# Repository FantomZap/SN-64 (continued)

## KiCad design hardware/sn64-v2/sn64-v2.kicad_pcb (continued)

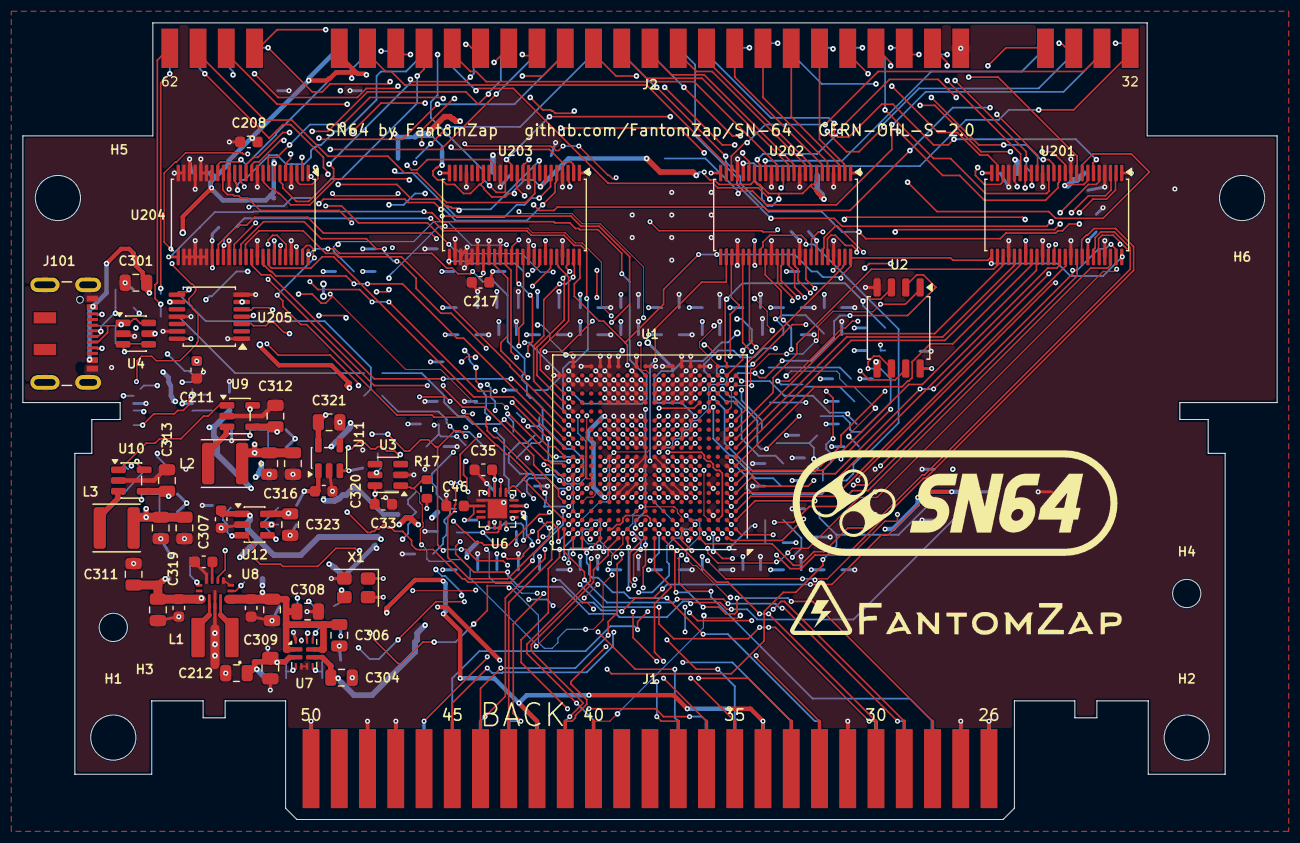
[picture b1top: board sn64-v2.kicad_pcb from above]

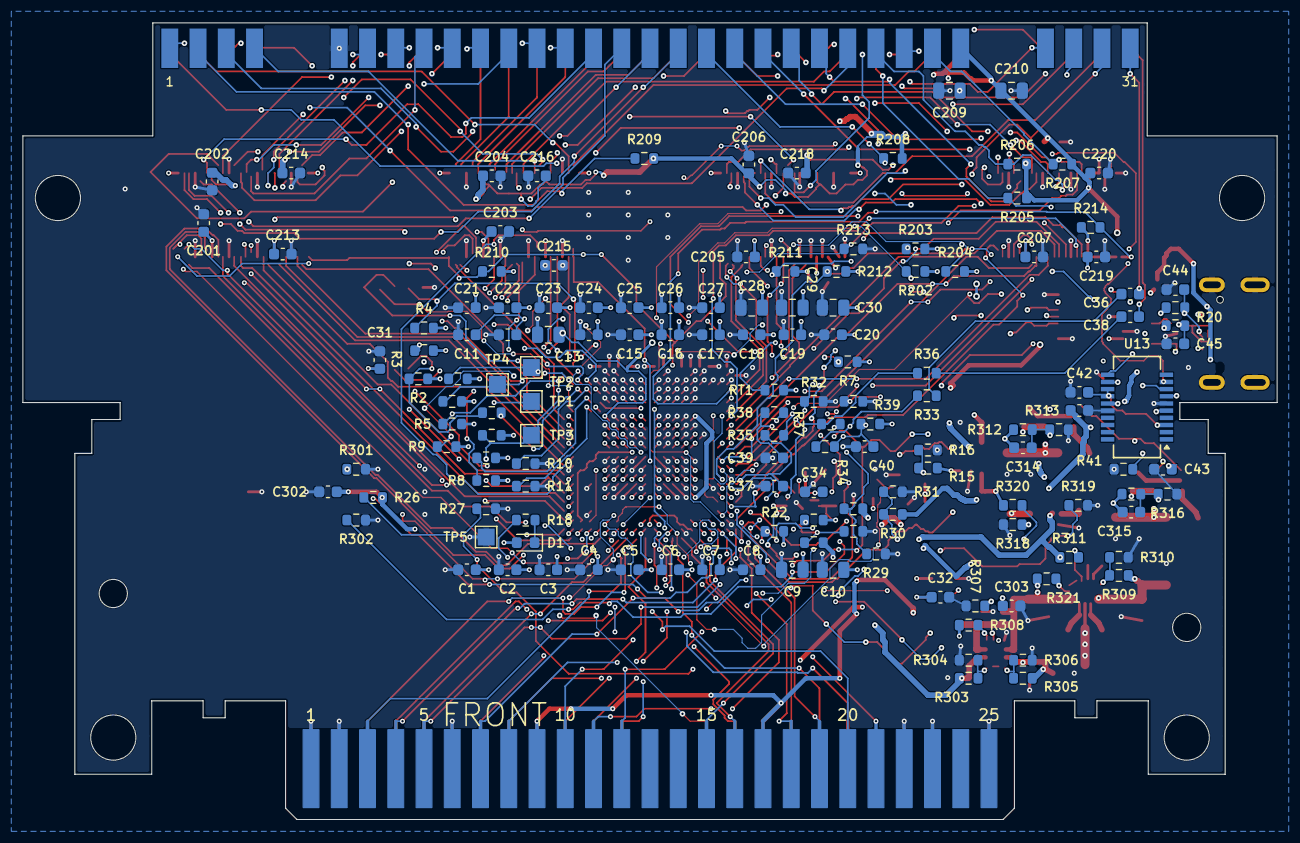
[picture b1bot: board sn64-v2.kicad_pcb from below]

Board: 6 copper layers, 111.0 x 70.5 mm, 200 parts (142 on the bottom side), 221 nets.

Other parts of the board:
H1, H2, H5, H6: MountingHole_4mm
H3, H4: MountingHole_2.5mm

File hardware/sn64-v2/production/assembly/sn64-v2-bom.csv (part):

Item,Designator,Qty,Manufacturer,Mfg Part #,Description / Value,Package / Footprint,Type,Side,LCSC or other source #,Substitute allowed,Notes
1,"C1, C2, C3, C4, C5, C6, C7, C8, C11, C12, C14, C15, C16, C17, C18, C19, C20, C21, C22, C23, C24, C25, C26, C27, C31, C32, C33, C41, C42, C43, C201, C202, C203, C204, C205, C206, C207, C208, C211, C213, C214, C215, C216, C217, C218, C219, C220, C307, C322",49,YAGEO,CC0603KRX7R9BB104,100 nF 50 V X7R 10 % 0603,0603,SMD,bottom and top,C14663,"yes: same value, size and dielectric, same voltage or higher",
2,"C9, C10, C13, C28, C29, C30, C212, C305, C306, C308, C323",11,Samsung Electro-Mechanics,CL21A106KAYNNNE,10 uF 25 V X5R 10 % 0805,0805,SMD,bottom and top,C15850,"yes: same value, size and dielectric, same voltage or higher",
3,"C34, C35, C36, C38, C40, C46, C302, C320",8,Samsung Electro-Mechanics,CL10A105KB8NNNC,1 uF 50 V X5R 10 % 0603,0603,SMD,bottom and top,C15849,"yes: same value, size and dielectric, same voltage or higher",
4,"C37, C39",2,Samsung Electro-Mechanics,CL10C102JB8NNNC,1 nF 50 V C0G 5 % 0603,0603,SMD,bottom,C163508,"yes: same value, size and dielectric, same voltage or higher",
5,"C44, C45",2,Samsung Electro-Mechanics,CL10C470JB8NNNC,47 pF 50 V C0G 5 % 0603,0603,SMD,bottom,C1671,"yes: same value, size and dielectric, same voltage or higher",
6,"C209, C210, C309, C310, C311, C312, C313, C316, C317, C318, C319",11,Samsung Electro-Mechanics,CL21A226MAQNNNE,22 uF 25 V X5R 20 % 0805,0805,SMD,bottom and top,C45783,"yes: same value, size and dielectric, same voltage or higher",
7,C301,1,Samsung Electro-Mechanics,CL21A225KBQNNNE,2.2 uF 50 V X5R 10 % 0805,0805,SMD,top,C377773,"yes: same value, size and dielectric, same voltage or higher",
8,C303,1,FH (Fenghua),0603B103K500NT,10 nF 50 V X7R 10 % 0603,0603,SMD,bottom,C57112,"yes: same value, size and dielectric, same voltage or higher",
9,"C304, C321",2,Samsung Electro-Mechanics,CL21A475KAQNNNE,4.7 uF 25 V X5R 10 % 0805,0805,SMD,top,C1779,"yes: same value, size and dielectric, same voltage or higher",
10,"C314, C315",2,FH (Fenghua),0603CG6R8C500NT,6.8 pF 50 V C0G 0.25 pF 0603,0603,SMD,bottom,C1679,"yes: same value, size and dielectric, same voltage or higher",
11,"C324, C325",2,Samsung Electro-Mechanics,CL10A106MA8NRNC,10 uF 25 V X5R 20 % 0603,0603,SMD,top,C96446,"yes: same value, size and dielectric, same voltage or higher",
12,D1,1,Everlight,19-21SYGC/S530-E2/4T,"LED yellow-green 573 nm, 2.0 V, 0603",0603,SMD,bottom,C2986011,yes: any yellow-green 0603 lamp with about 2 V across it,
13,J101,1,JAE,DX07S016JA3R1500,DX07S016JA3R1500. USB 2.0-only Type-C Receptacle connector,"USB-C receptacle, 16 pads and 4 legs in plated slots",SMD,top,C2939926,no,USB-C: surface-mount pads and four legs in plated slots
14,L1,1,APV,PNR4020-1R5M,1.5uH PNR4020-1R5M. Inductor,4 x 4 x 2 mm inductor,SMD,top,C54620133,no,
15,"L2, L3",2,Changjiang Microelectronics,FNR4030S2R2MT,2.2uH FNR4030S2R2MT. Inductor,4 x 4 x 3 mm inductor,SMD,top,C167869,no,
16,R1,1,UNI-ROYAL,0603WAF330JT5E,33 ohm 1 % 0603,0603,SMD,bottom,C23140,"yes: same value, size and tolerance",
17,"R2, R18",2,UNI-ROYAL,0603WAF1001T5E,1 k 1 % 0603,0603,SMD,bottom,C21190,"yes: same value, size and tolerance",
18,"R3, R6, R7, R8, R9, R12, R13, R14, R22, R23, R41, R205, R206, R207, R208",15,UNI-ROYAL,0603WAF4701T5E,4.7 k 1 % 0603,0603,SMD,bottom,C23162,"yes: same value, size and tolerance",
19,"R4, R5, R10, R11, R17, R24, R25, R27, R29, R31, R32, R33, R34, R35, R36, R37, R38, R39, R40, R202, R203, R204, R209, R308, R320, R321",26,UNI-ROYAL,0603WAF1002T5E,10 k 1 % 0603,0603,SMD,bottom and top,C25804,"yes: same value, size and tolerance",
20,R15,1,FOJAN,FRC0603F6493TS,649 k 1 % 0603,0603,SMD,bottom,C2999594,"yes: same value, size and tolerance",
21,"R16, R210, R211, R212, R213, R214, R304, R306, R311, R319",10,UNI-ROYAL,0603WAF1003T5E,100 k 1 % 0603,0603,SMD,bottom,C25803,"yes: same value, size and tolerance",
22,"R19, R20",2,UNI-ROYAL,0603WAF270JT5E,27 ohm 1 % 0603,0603,SMD,bottom,C25190,"yes: same value, size and tolerance",
23,"R26, R28, R30",3,UNI-ROYAL,0603WAF2002T5E,20 k 1 % 0603,0603,SMD,bottom,C4184,"yes: same value, size and tolerance",
24,"R301, R302",2,UNI-ROYAL,0603WAF5101T5E,5.1 k 1 % 0603,0603,SMD,bottom,C23186,"yes: same value, size and tolerance",
25,R303,1,FOJAN,FRC0603F2743TS,274 k 1 % 0603,0603,SMD,bottom,C5126128,"yes: same value, size and tolerance",
26,R305,1,FOJAN,FRC0603F1823TS,182 k 1 % 0603,0603,SMD,bottom,C5126102,"yes: same value, size and tolerance",
27,R307,1,FOJAN,FRC0603F4422TS,44.2 k 1 % 0603,0603,SMD,bottom,C2930103,"yes: same value, size and tolerance",
28,R309,1,YAGEO,RT0603BRD07232KL,232 k 0.1 % 25 ppm thin film 0603,0603,SMD,bottom,C861240,"yes: same value, size and tolerance",
29,R310,1,YAGEO,RT0603BRD0744K2L,44.2 k 0.1 % 25 ppm thin film 0603,0603,SMD,bottom,C861410,"yes: same value, size and tolerance",
30,R312,1,YAGEO,RT0603BRD07459KL,459 k 0.1 % 25 ppm thin film 0603,0603,SMD,bottom,C6288321,"yes: same value, size and tolerance",
31,R313,1,YAGEO,RT0603BRD07102KL,102 k 0.1 % 25 ppm thin film 0603,0603,SMD,bottom,C861068,"yes: same value, size and tolerance",
32,R315,1,YAGEO,RT0603BRD07100KL,100 k 0.1 % 25 ppm thin film 0603,0603,SMD,bottom,C122538,"yes: same value, size and tolerance",
33,R316,1,YAGEO,RT0603BRD07120KL,120 k 0.1 % 25 ppm thin film 0603,0603,SMD,bottom,C705720,"yes: same value, size and tolerance",
34,R318,1,UNI-ROYAL,0603WAF2492T5E,24.9 k 1 % 0603,0603,SMD,bottom,C25962,"yes: same value, size and tolerance",
35,RT1,1,Sunlord,SDNT1608X103F3950FTF,"NTC 10 k 1 %, B(25/50) 3950 K 1 %, 0603",0603,SMD,bottom,C279936,"yes: 10 k, 1 %, B(25/50) 3950 K, 0603",
36,U1,1,Lattice Semiconductor,LFE5U-85F-8BG381I,"LFE5U-85F-8BG381I. ECP5 FPGA, 84K LUTs, 1.2V, BGA-381","caBGA-381, 0.8 mm pitch",SMD,top,Mouser 842-LFE5U85F8BG381I,no,
37,U2,1,Winbond,W25Q128JVSIQ,"W25Q128JVSIQ. 128Mbit / 16MiB Serial Flash Memory, Standard/Dual/Quad SPI, 2.7-3.6V, SOIC-8","SOIC-8, 5.3 mm body",SMD,top,C97521,no,
38,U3,1,Texas Instruments,TPS3808G01DBVR,"TPS3808G01DBVR. Low-Quiescent-Current, Programmable-Delay Supervisory Circuit, SOT-23-6",SOT-23-6,SMD,top,C19653,no,
39,U4,1,STMicroelectronics,USBLC6-2SC6,"USBLC6-2SC6. Very low capacitance ESD protection diode, 2 data-line, SOT-23-6",SOT-23-6,SMD,top,C7519,no,
40,U6,1,Texas Instruments,TLA2528IRTER,"TLA2528IRTER. 8-channel 12-bit I2C ADC, WQFN-16","WQFN-16, 3 x 3 mm, 0.5 mm pitch",SMD,top,C2866175,no,
41,U7,1,Texas Instruments,TPS2121RUXR,"TPS2121RUXR. 2.8-22 V priority power mux, 4.5 A, current limit, VQFN-HR-12","VQFN-HR-12, 2 x 2.5 mm",SMD,top,C485916,no,
42,U8,1,Texas Instruments,TPS63070RNMR,"TPS63070RNMR. 2-16 V input buck-boost converter, adjustable output, power good","VQFN-HR-15, 2.5 x 3 mm",SMD,top,C109322,no,
43,"U9, U10",2,Texas Instruments,TLV62569DBVR,"TLV62569DBVR. High Efficiency Synchronous Buck Converter, Adjustable Output 0.6V-5.5V, 2A, SOT-23-5",SOT-23-5,SMD,top,C141836,no,
44,U11,1,Diodes Incorporated,AP2112K-2.5TRG1,"AP2112K-2.5TRG1. 600mA low dropout linear regulator, with enable pin, 3V-6V input voltage range, 2.5V fixed positive output, SOT-23-5",SOT-23-5,SMD,top,C51118,no,
45,U12,1,Texas Instruments,TPS2553DBVR,"TPS2553DBVR. Power-distribution switch 1.5 A, adjustable current limit, fault flag, SOT-23-6",SOT-23-6,SMD,top,C55266,no,
46,U13,1,FTDI,FT231XS-R,"FT231XS-R. Full Speed USB to Full Handshake UART, SSOP-20","SSOP-20, 0.635 mm pitch",SMD,bottom,C132160,no,
47,"U201, U202, U203, U204",4,Texas Instruments,SN74ALVC164245DGGR,"SN74ALVC164245DGGR. 16-Bit 2.5V to 3.3V or 3.3V to 5V Level-Shifting Transceiver With 3-State Outputs, TSSOP-48","TSSOP-48, 0.5 mm pitch",SMD,top,C7128,no,
48,U205,1,Texas Instruments,SN74LVC07APWR,"SN74LVC07APWR. Hex buffer with open-drain outputs, TSSOP-14",TSSOP-14,SMD,top,C7809,no,
49,X1,1,Interquip,1631-27005-BTBEYA,"27MHz 1631-27005-BTBEYA. 27 MHz CMOS oscillator, 3.3 V, 50 ppm, 3.2 x 2.5 mm, 4 pads","3.2 x 2.5 mm, 4 pads",SMD,top,C3003262,no,

,Not fitted by the assembler
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
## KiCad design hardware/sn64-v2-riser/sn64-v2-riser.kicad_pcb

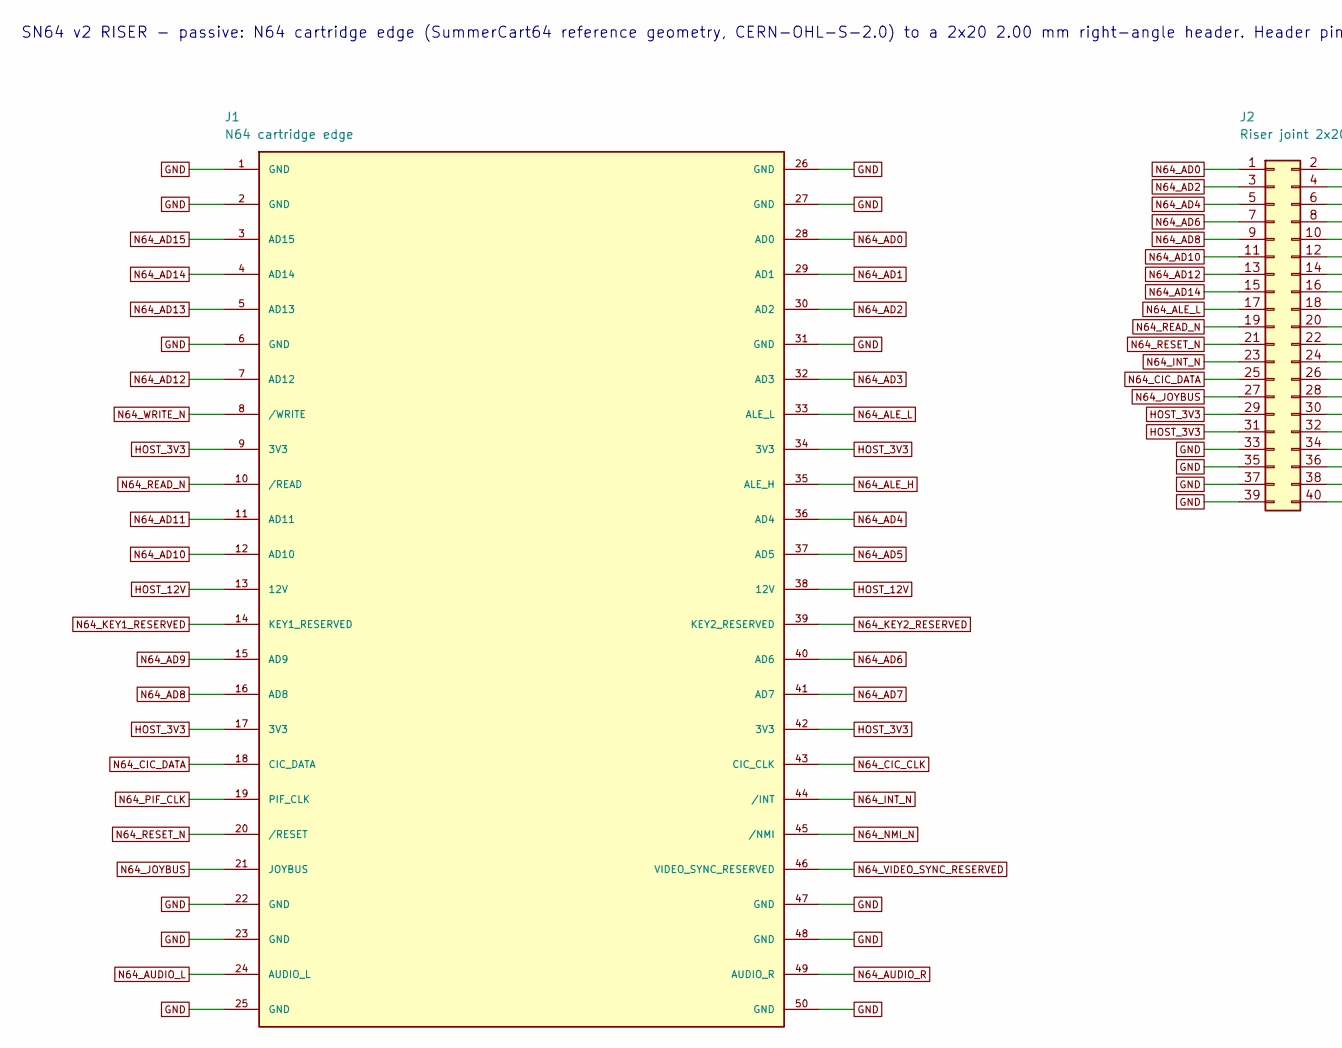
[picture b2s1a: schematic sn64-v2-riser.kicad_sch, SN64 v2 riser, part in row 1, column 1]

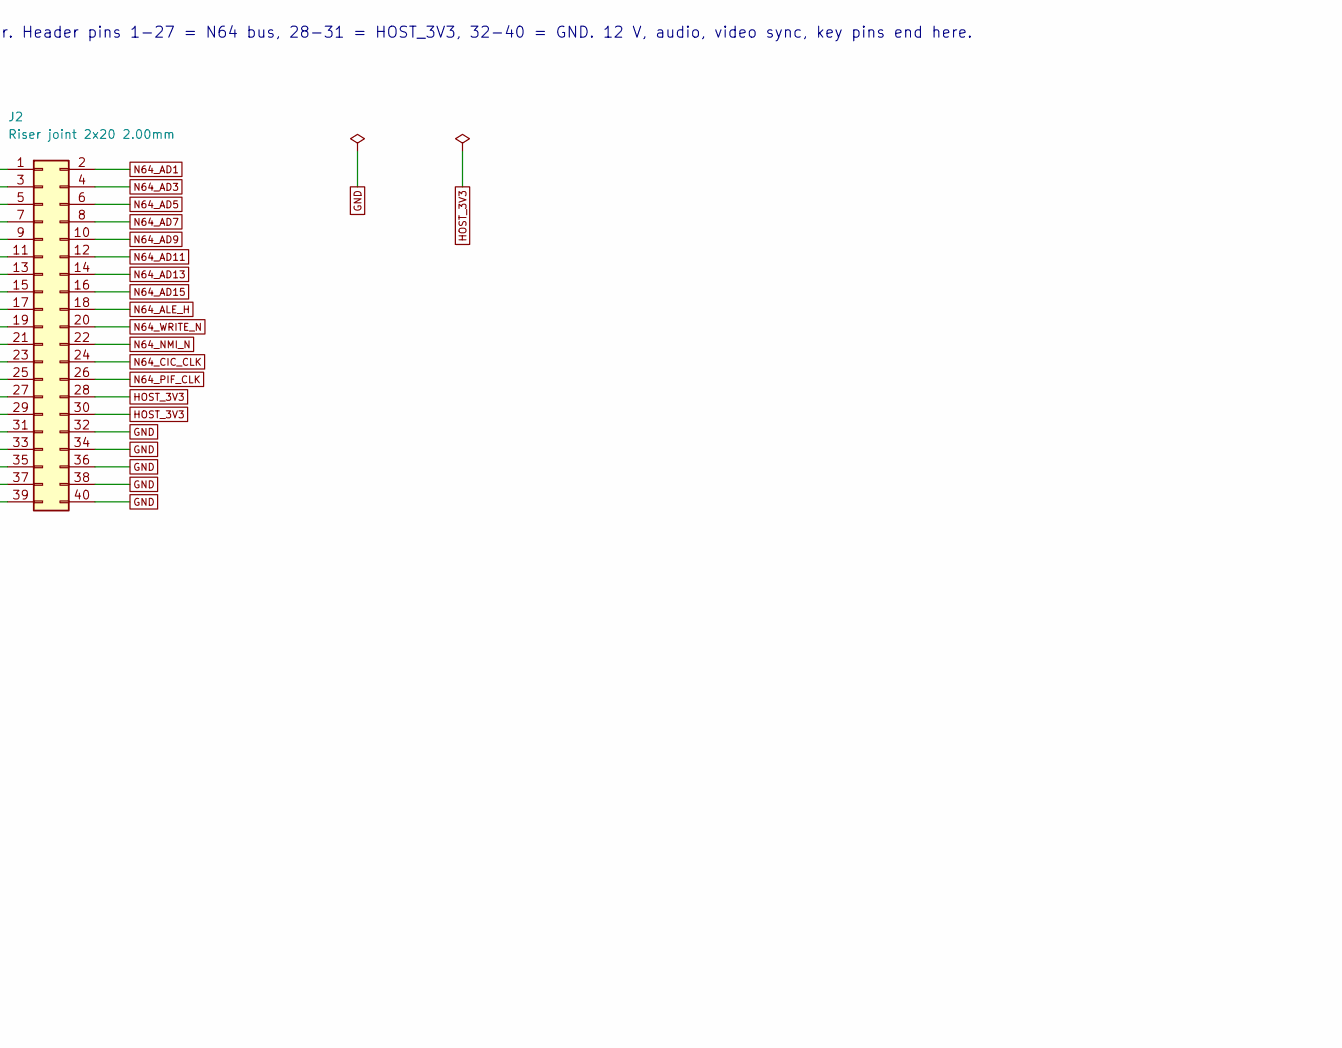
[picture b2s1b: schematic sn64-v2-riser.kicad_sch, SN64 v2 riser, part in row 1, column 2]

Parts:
J1: N64 cartridge edge; N64_Edge_SC64_Reference
J2: Riser joint 2x20 2.00mm; PinHeader_2x20_P2.00mm_Horizontal

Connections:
GND: J1.1 (GND), J1.2 (GND), J1.6 (GND), J1.22 (GND), J1.23 (GND), J1.25 (GND), J1.26 (GND), J1.27 (GND), J1.31 (GND), J1.47 (GND), J1.48 (GND), J1.50 (GND), J2.32, J2.33, J2.34, J2.35, J2.36, J2.37, J2.38, J2.39, J2.40
HOST_3V3: J1.9 (3V3), J1.17 (3V3), J1.34 (3V3), J1.42 (3V3), J2.28, J2.29, J2.30, J2.31
HOST_12V: J1.13 (12V), J1.38 (12V)
N64_AD0: J1.28 (AD0), J2.1
N64_AD1: J1.29 (AD1), J2.2
N64_AD2: J1.30 (AD2), J2.3
N64_AD3: J1.32 (AD3), J2.4
N64_AD4: J1.36 (AD4), J2.5
N64_AD5: J1.37 (AD5), J2.6
N64_AD6: J1.40 (AD6), J2.7
N64_AD7: J1.41 (AD7), J2.8
N64_AD8: J1.16 (AD8), J2.9
N64_AD9: J1.15 (AD9), J2.10
N64_AD10: J1.12 (AD10), J2.11
N64_AD11: J1.11 (AD11), J2.12
N64_AD12: J1.7 (AD12), J2.13
N64_AD13: J1.5 (AD13), J2.14
N64_AD14: J1.4 (AD14), J2.15
N64_AD15: J1.3 (AD15), J2.16
N64_ALE_H: J1.35 (ALE_H), J2.18
N64_ALE_L: J1.33 (ALE_L), J2.17
N64_AUDIO_L: J1.24 (AUDIO_L)
N64_AUDIO_R: J1.49 (AUDIO_R)
N64_CIC_CLK: J1.43 (CIC_CLK), J2.24
N64_CIC_DATA: J1.18 (CIC_DATA), J2.25
N64_INT_N: J1.44 (/INT), J2.23
N64_JOYBUS: J1.21 (JOYBUS), J2.27
N64_KEY1_RESERVED: J1.14 (KEY1_RESERVED)
N64_KEY2_RESERVED: J1.39 (KEY2_RESERVED)
N64_NMI_N: J1.45 (/NMI), J2.22
N64_PIF_CLK: J1.19 (PIF_CLK), J2.26
N64_READ_N: J1.10 (/READ), J2.19
N64_RESET_N: J1.20 (/RESET), J2.21
N64_VIDEO_SYNC_RESERVED: J1.46 (VIDEO_SYNC_RESERVED)
N64_WRITE_N: J1.8 (/WRITE), J2.20

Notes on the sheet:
SN64 v2 RISER - passive: N64 cartridge edge (SummerCart64 reference geometry, CERN-OHL-S-2.0) to a 2x20 2.00 mm right-angle header. Header pins 1-27 = N64 bus, 28-31 = HOST_3V3, 32-40 = GND. 12 V, audio, video sync, key pins end here.

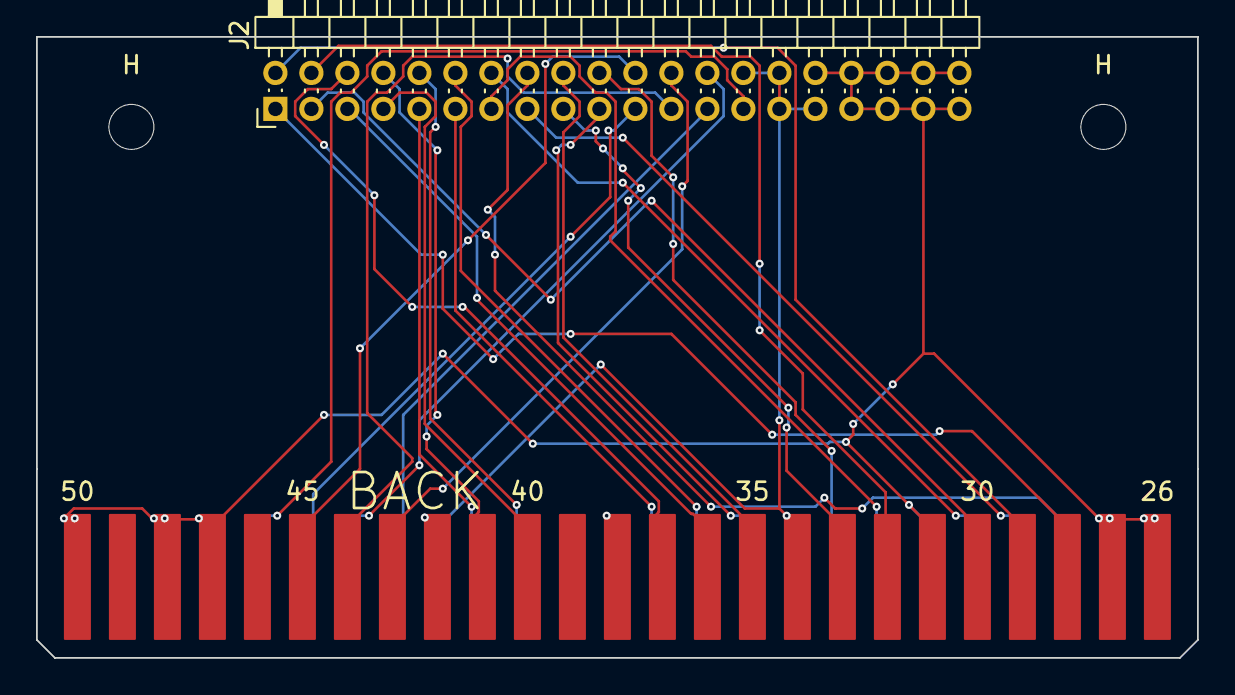
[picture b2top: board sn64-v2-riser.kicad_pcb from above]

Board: 2 copper layers, 64.5 x 34.5 mm, 4 parts (0 on the bottom side), 30 nets.

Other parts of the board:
H: MountingHole_2.5mm
H#2: MountingHole_2.5mm
